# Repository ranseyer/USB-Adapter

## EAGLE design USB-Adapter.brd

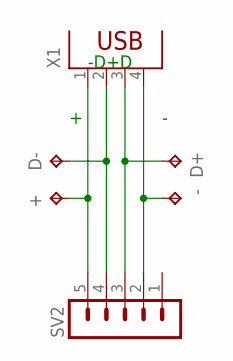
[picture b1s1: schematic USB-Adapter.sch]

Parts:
+: TPPAD1-13; P1-13
-: TPPAD1-13; P1-13
D+: TPPAD1-13; P1-13
D-: TPPAD1-13; P1-13
SV2: MA05-1
X1: PN87520

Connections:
+: +.TP, SV2.5, X1.1
D+: D+.TP, SV2.3, X1.3
D-: D-.TP, SV2.4, X1.2
GND: -.TP, SV2.2, X1.4

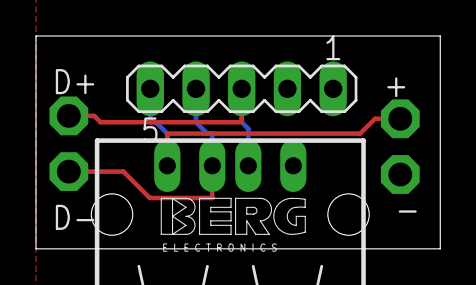
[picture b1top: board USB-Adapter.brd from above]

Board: 2 copper layers, 22.5 x 11.8 mm, 6 parts (0 on the bottom side), 4 nets.

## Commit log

2014-05-15 Upload
